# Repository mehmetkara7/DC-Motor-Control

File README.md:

# DC-Motor-Control
# Motor Control with ACS712 Current Sensor and Atmega324PB Microcontroller

This project demonstrates motor control using an ACS712 current sensor with an Atmega324PB microcontroller. The microcontroller controls the motor speed and direction based on the current measured by the ACS712 sensor.

## Components

- Atmega324PB microcontroller
- ACS712 current sensor
- Motor driver circuit
- Buzzer
- Relay
- Other necessary components (e.g., resistors, capacitors, power supply)

## Getting Started

1. Clone or download this repository to your local machine.
2. Connect the components as shown in the circuit diagram.
3. Compile and upload the code to your Atmega324PB microcontroller using an AVR programmer.
4. Power up the circuit and observe the motor control based on current readings.

## Code Explanation

- `setup()`: Initializes the microcontroller pins and sets up the Timer/Counter1 for PWM control.
- `setMotorSpeed(uint8_t speed)`: Sets the motor speed using PWM (Pulse Width Modulation).
- `forward()`, `backward()`, `stop()`: Functions to control the motor direction.
- `turnOnRelay()`, `turnOffRelay()`: Functions to control the relay.
- `turnOnBuzzer()`, `turnOffBuzzer()`: Functions to control the buzzer.
- `readACS712()`: Reads the current value from the ACS712 sensor.
- `main()`: The main control loop that reads current values and adjusts motor control accordingly.

## Usage

Modify the code as needed to adjust the current threshold for motor control and the motor speed settings.

```c
if (adcValue > 512) {
    // Current threshold exceeded, take action (e.g., stop motor and sound buzzer)
} else {
    // Current within the acceptable range, adjust motor speed and direction as needed
    // Example: forward(), setMotorSpeed(speed), _delay_ms(delay);
}

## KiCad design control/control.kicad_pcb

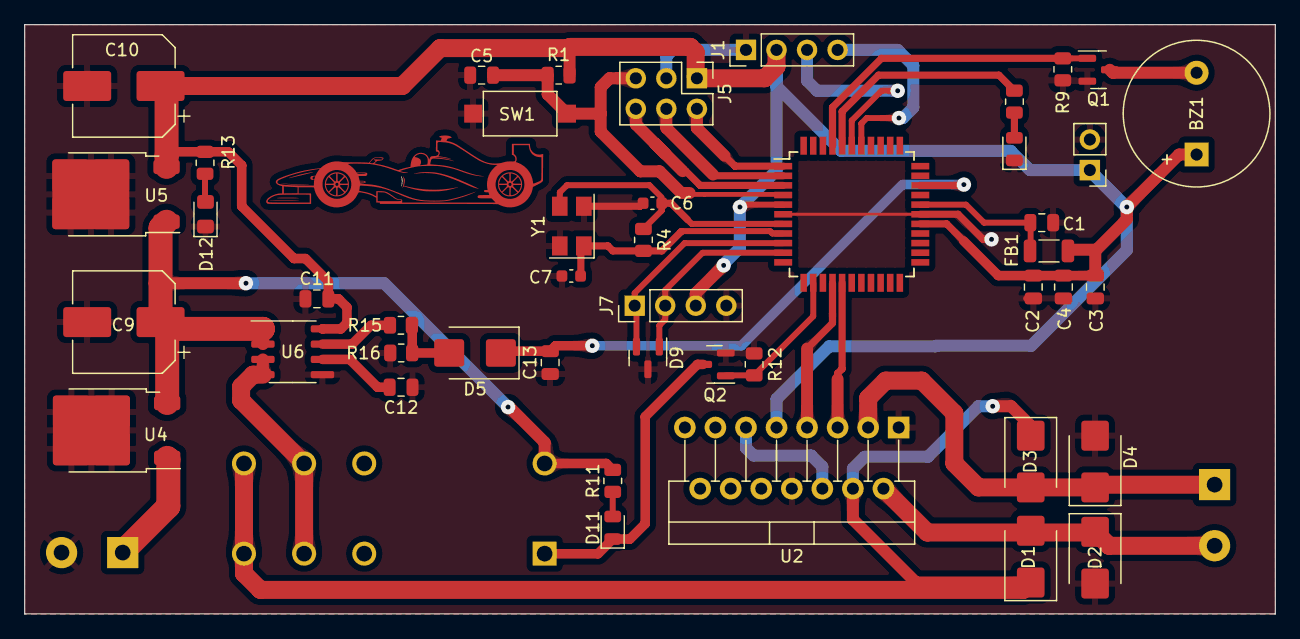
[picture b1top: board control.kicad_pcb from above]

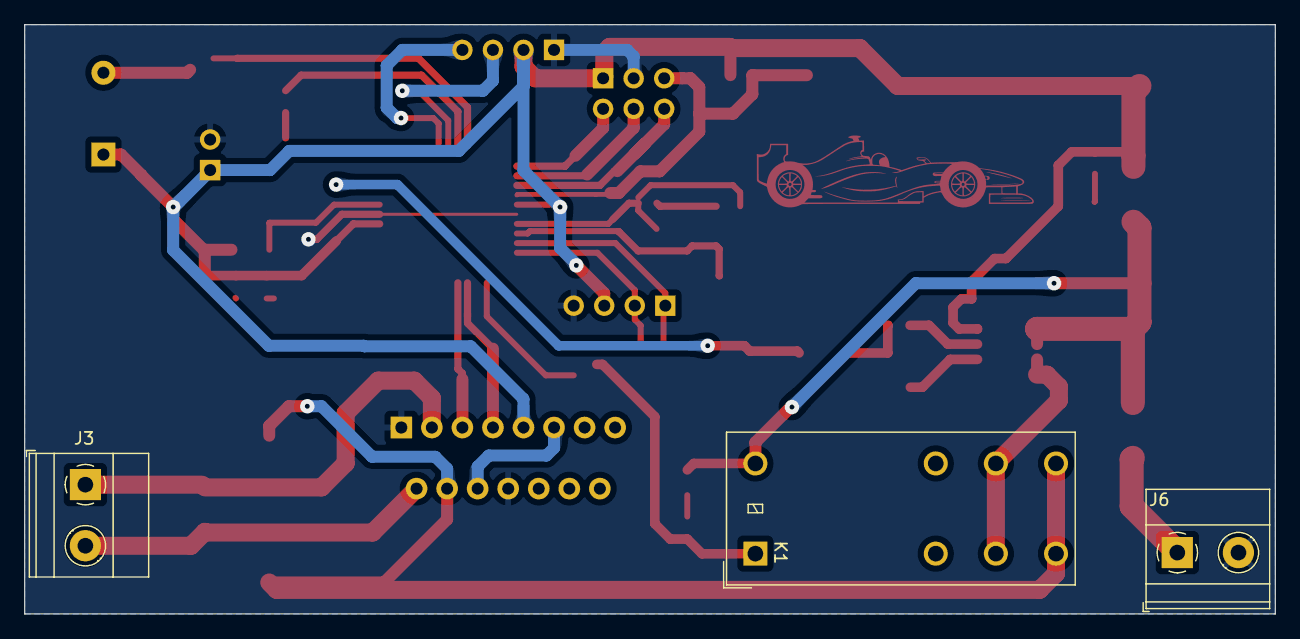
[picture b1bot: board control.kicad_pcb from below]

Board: 2 copper layers, 104.0 x 49.0 mm, 48 parts (3 on the bottom side), 34 nets.

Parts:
BZ1: Buzzer; Buzzer_12x9.5RM7.6
C1: 1uF; C_0805_2012Metric
C2, C3, C4, C5, C11: 100nF; C_0805_2012Metric
C6, C7: 18pF; C_0603_1608Metric
C9, C10: 220uf; CP_Elec_8x6.7
C12, C13: 1nF; C_0805_2012Metric
D1, D2, D3, D4: D_Small; D_SMB
D5: SS24; D_SMB
D9: SM712_SOT23; SOT-23
D11, D13: LED_Small; LED_0805_2012Metric
D12: LED_Small; LED_0805_2012Metric_Pad1.15x1.40mm_HandSolder
FB1: 120R; L_1206_3216Metric
J1: I2C; PinHeader_1x04_P2.54mm_Vertical
J3: Conn_01x02; TerminalBlock_Phoenix_MKDS-1,5-2-5.08_1x02_P5.08mm_Horizont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
J5: ISP; PinHeader_2x03_P2.54mm_Vertical
J6: POWER; TerminalBlock_Phoenix_MKDS-1,5-2-5.08_1x02_P5.08mm_Horizont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
J7: UART; PinHeader_1x04_P2.54mm_Vertical
J10: Conn_01x02; PinHeader_1x02_P2.54mm_Vertical
K1: G2RL-2; Relay_DPDT_Omron_G2RL-2
Q1, Q2: 2N7002; SOT-23
R1: 4K7; R_0805_2012Metric
R4: 1M; R_0805_2012Metric
R9, R12, R16: 10K; R_0805_2012Metric
R11, R14: 1K; R_0805_2012Metric
R13: 1k; R_0805_2012Metric
R15: 2K2; R_0805_2012Metric
SW1: 6x6 SMD; SW_SPST_CK_RS282G05A3
U1: ATmega324PB-A; TQFP-44_10x10mm_P0.8mm
U2: L298N; TO-220-15_P2.54x2.54mm_StaggerOdd_Lead4.58mm_Vertical
U4: L7812; TO-252-2
U5: LM78M05_TO252; TO-252-2
U6: ACS712; SOIC-8_3.9x4.9mm_P1.27mm
Y1: 16MHz; Crystal_SMD_5032-4Pin_5.0x3.2mm

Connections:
+5V: BZ1.1 (-), C2.1, C3.1, C4.1, C10.1, C11.2, FB1.1, J1.2, J5.1, J7.3, J10.1, R1.1, R13.1, U1.5 (VCC), U1.27 (AVCC), U2.9 (Vss), U5.3 (VO), U6.8 (VCC)
BUZZER: Q1.1 (G), R9.1, U1.41 (PB1)
CURRENT_ADC1: C13.2, D5.1 (K), U1.31 (PA6)
GND: C1.2, C2.2, C3.2, C4.2, C5.2, C6.2, C7.2, C9.2, C10.2, C11.1, C12.1, C13.1, D2.2 (A), D4.2 (A), D9.3 (common), D12.1 (K), D13.1 (K), J1.1, J5.3, J6.2, J7.4, J10.2, Q1.2 (S), Q2.2 (S), R9.2, R12.2, R16.1, SW1.2, U1.6 (GND), U1.28 (GND), U2.1 (SENSE_A), U2.8 (GND), U4.2 (GND), U5.2 (GND), U6.5 (GND), Y1.2, Y1.4
IN1: U1.16 (PD7), U2.5 (IN1)
IN2: U1.15 (PD6), U2.7 (IN2)
IN+: C9.1, K1.A2, R11.2, U4.3 (OUT), U5.1 (VI), U6.1 (IP+), U6.2 (IP+)
IN-: K1.11, K1.21, U6.3 (IP-), U6.4 (IP-)
LED: R14.2, U1.40 (PB0)
MISO: J5.4, U1.2 (PB6)
MOSI: J5.2, U1.1 (PB5)
unnamed: BZ1.2 (+), Q1.3 (D)
unnamed: D5.2 (A), R15.2, R16.2
unnamed: D11.2 (A), R11.1
unnamed: D11.1 (K), K1.A1, Q2.3 (D)
unnamed: D12.2 (A), R13.2
unnamed: D13.2 (A), R14.1
unnamed: J6.1, U4.1 (IN)
unnamed: C1.1, FB1.2, U1.29 (PE4/AREF)
unnamed: U2.6 (EnA), U2.11 (EnB)
unnamed: C12.2, U6.6 (FILTER)
unnamed: R15.1, U6.7 (VIOUT)
OUT1: D1.2 (A), D2.1 (K), J3.2, U2.2 (OUT1)
OUT2: D3.2 (A), D4.1 (K), J3.1, U2.3 (OUT2)
RELAY: Q2.1 (G), R12.1, U1.13 (PD4)
RELAY+: D1.1 (K), D3.1 (K), K1.14, K1.24, U2.4 (Vs)
RESET: C5.1, J5.5, R1.2, SW1.1, U1.4 (~RESET)
RX0: D9.2 (A2), J7.1, U1.9 (PD0)
SCK: J5.6, U1.3 (PB7)
SCL1: J1.3, U1.39 (PE6)
SDA1: J1.4, U1.38 (PE5)
TX0: D9.1 (A1), J7.2, U1.10 (PD1)
XTAL1: C7.1, R4.1, U1.8 (PE1/XTAL1), Y1.1
XTAL2: C6.1, R4.2, U1.7 (PE0/XTAL2), Y1.3

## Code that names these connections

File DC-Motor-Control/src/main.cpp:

#include <avr/io.h>
#include <util/delay.h>

#define MOTOR_IN1 PD6
#define MOTOR_IN2 PD7
#define PWM_PIN PD5
#define RELAY_PIN PD4
#define BUZZER_PIN PB1

void setup()
{
  DDRD |= (1 << MOTOR_IN1) | (1 << MOTOR_IN2) | (1 << PWM_PIN) | (1 << RELAY_PIN);
  PORTD &= ~((1 << MOTOR_IN1) | (1 << MOTOR_IN2) | (1 << RELAY_PIN));

  TCCR1A = (1 << COM1A1) | (1 << WGM11) | (1 << WGM10);
  TCCR1B = (1 << WGM12) | (1 << CS11);

  DDRB |= (1 << BUZZER_PIN);
  PORTB &= ~(1 << BUZZER_PIN);
}

void setMotorSpeed(uint8_t speed)
{
  OCR1A = speed;
}

void forward()
{
  PORTD |= (1 << MOTOR_IN1);
  PORTD &= ~(1 << MOTOR_IN2);
}

void backward()
{
  PORTD &= ~(1 << MOTOR_IN1);
  PORTD |= (1 << MOTOR_IN2);
}

void stop()
{
  PORTD &= ~((1 << MOTOR_IN1) | (1 << MOTOR_IN2));
}

void turnOnRelay()
{
  PORTD |= (1 << RELAY_PIN);
}

void turnOffRelay()
{
  PORTD &= ~(1 << RELAY_PIN);
}

void turnOnBuzzer()
{
  PORTB |= (1 << BUZZER_PIN);
}

void turnOffBuzzer()
{
  PORTB &= ~(1 << BUZZER_PIN);
}

uint16_t readACS712()
{
  ADCSRA |= (1 << ADSC);
  while (ADCSRA & (1 << ADSC))
    ;
  return ADC;
}

int main(void)
{
  setup();
  turnOnRelay();

  while (1)
  {
    uint16_t adcValue = readACS712();
    if (adcValue > 512)
    {
      stop();
      turnOffRelay();
      turnOnBuzzer();
    }
    else
    {
      turnOnRelay();
      forward();
      setMotorSpeed(100);
      _delay_ms(2000);
      setMotorSpeed(150);
      _delay_ms(1000);
      setMotorSpeed(200);
      _delay_ms(2000);

      backward();
      setMotorSpeed(100);
      _delay_ms(2000);
    }
  }

  return 0;
}

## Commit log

2023-09-04 README.md
